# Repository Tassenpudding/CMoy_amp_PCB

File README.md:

# CMoy_amp_PCB

simple PCB created in EAGLE for the CMoy Headphone amplifier

Schematic from:
https://tangentsoft.net/audio/cmoy/

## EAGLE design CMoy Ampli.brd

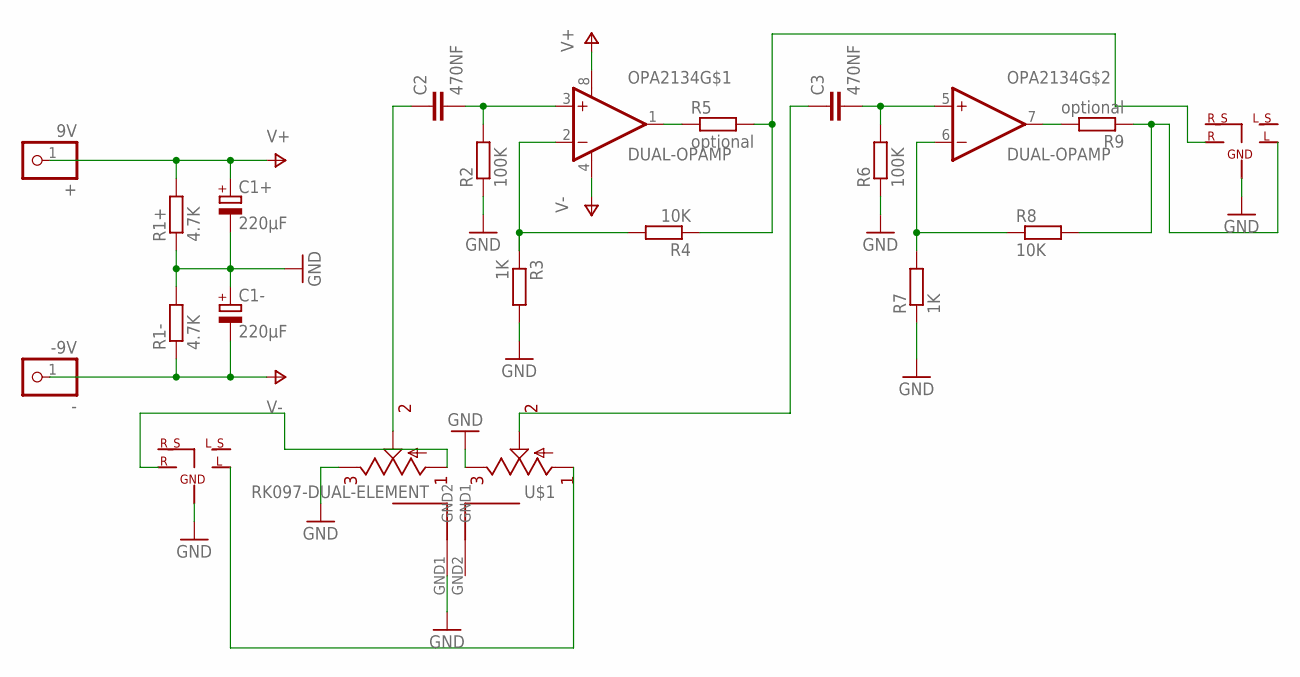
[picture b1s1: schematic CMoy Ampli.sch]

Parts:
+: 9V; 1X01
-: -9V; 1X01
C1+, C1-: 220µF; E3,5-8
C2, C3: 470NF; C075-042X103
OPA2134: DUAL-OPAMP; DIP-8
R1+, R1-: 4.7K; 0309V
R2, R6: 100K; 0309V
R3, R7: 1K; 0309V
R4, R8: 10K; 0309V
R5, R9: optional; 0309V
U$1: RK097-DUAL-ELEMENT
U$2, U$3: EBS35

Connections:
GND: C1+.-, C1-.+, R1+.1, R1-.2, R2.1, R3.2, R6.1, R7.1, U$1.GND1 (GND2), U$1.IN1, U$1.IN2, U$2.GND, U$3.GND
L: C3.1, U$1.AMP2
L+: C3.2, OPA2134.5 (+IN), R6.2
L-: OPA2134.6 (-IN), R7.2, R8.1
L_IN: U$1.GND12, U$2.L
L_OUT: R8.2, R9.1, U$3.L
unnamed: OPA2134.2 (-IN), R3.1, R4.2
unnamed: OPA2134.1 (OUT), R5.1
OPT_L: OPA2134.7 (OUT), R9.2
R: C2.1, U$1.AMP1
R+: C2.2, OPA2134.3 (+IN), R2.2
R_IN: U$1.GND11, U$2.R
R_OUT: R4.1, R5.2, U$3.R
V+: +.1, C1+.+, OPA2134.8 (V+), R1+.2
V-: -.1, C1-.-, OPA2134.4 (V-), R1-.1

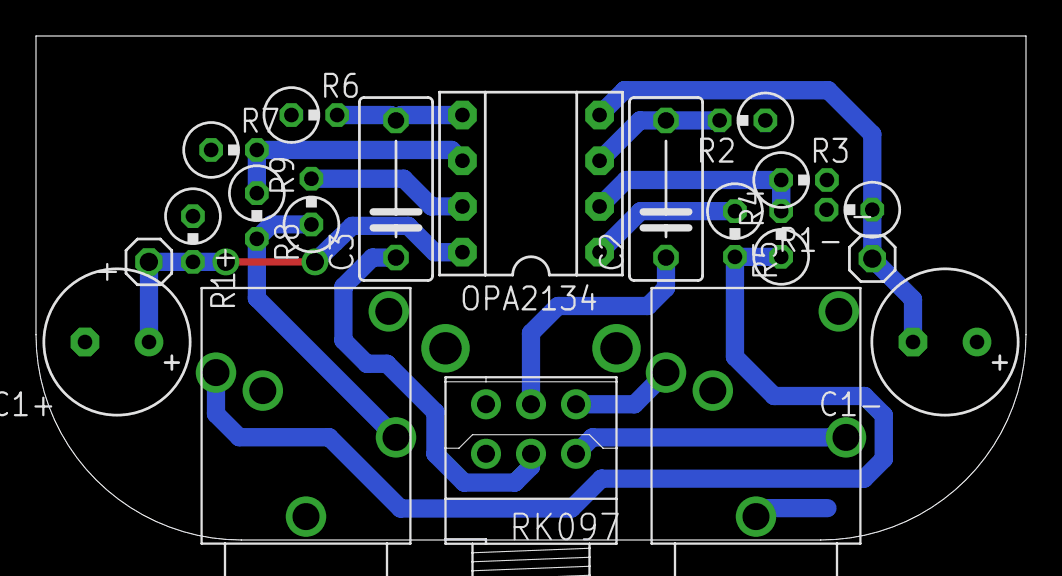
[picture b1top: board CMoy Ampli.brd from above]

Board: 2 copper layers, 55.0 x 28.0 mm, 20 parts (0 on the bottom side), 15 nets.

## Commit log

2018-11-30 init commit
2019-09-11 add .gitignore
2019-09-11 remove eagle.epf
